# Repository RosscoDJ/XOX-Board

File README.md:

# XOX-Board
xox style board with 16 buttons and 16 less connected to two MCP23017 I/O extenders for I2C communications with micro controllers. Full Schmitt trigger hardware debouncing per button, and SMD jumper pads for addressing MCP23017 IC's on board.

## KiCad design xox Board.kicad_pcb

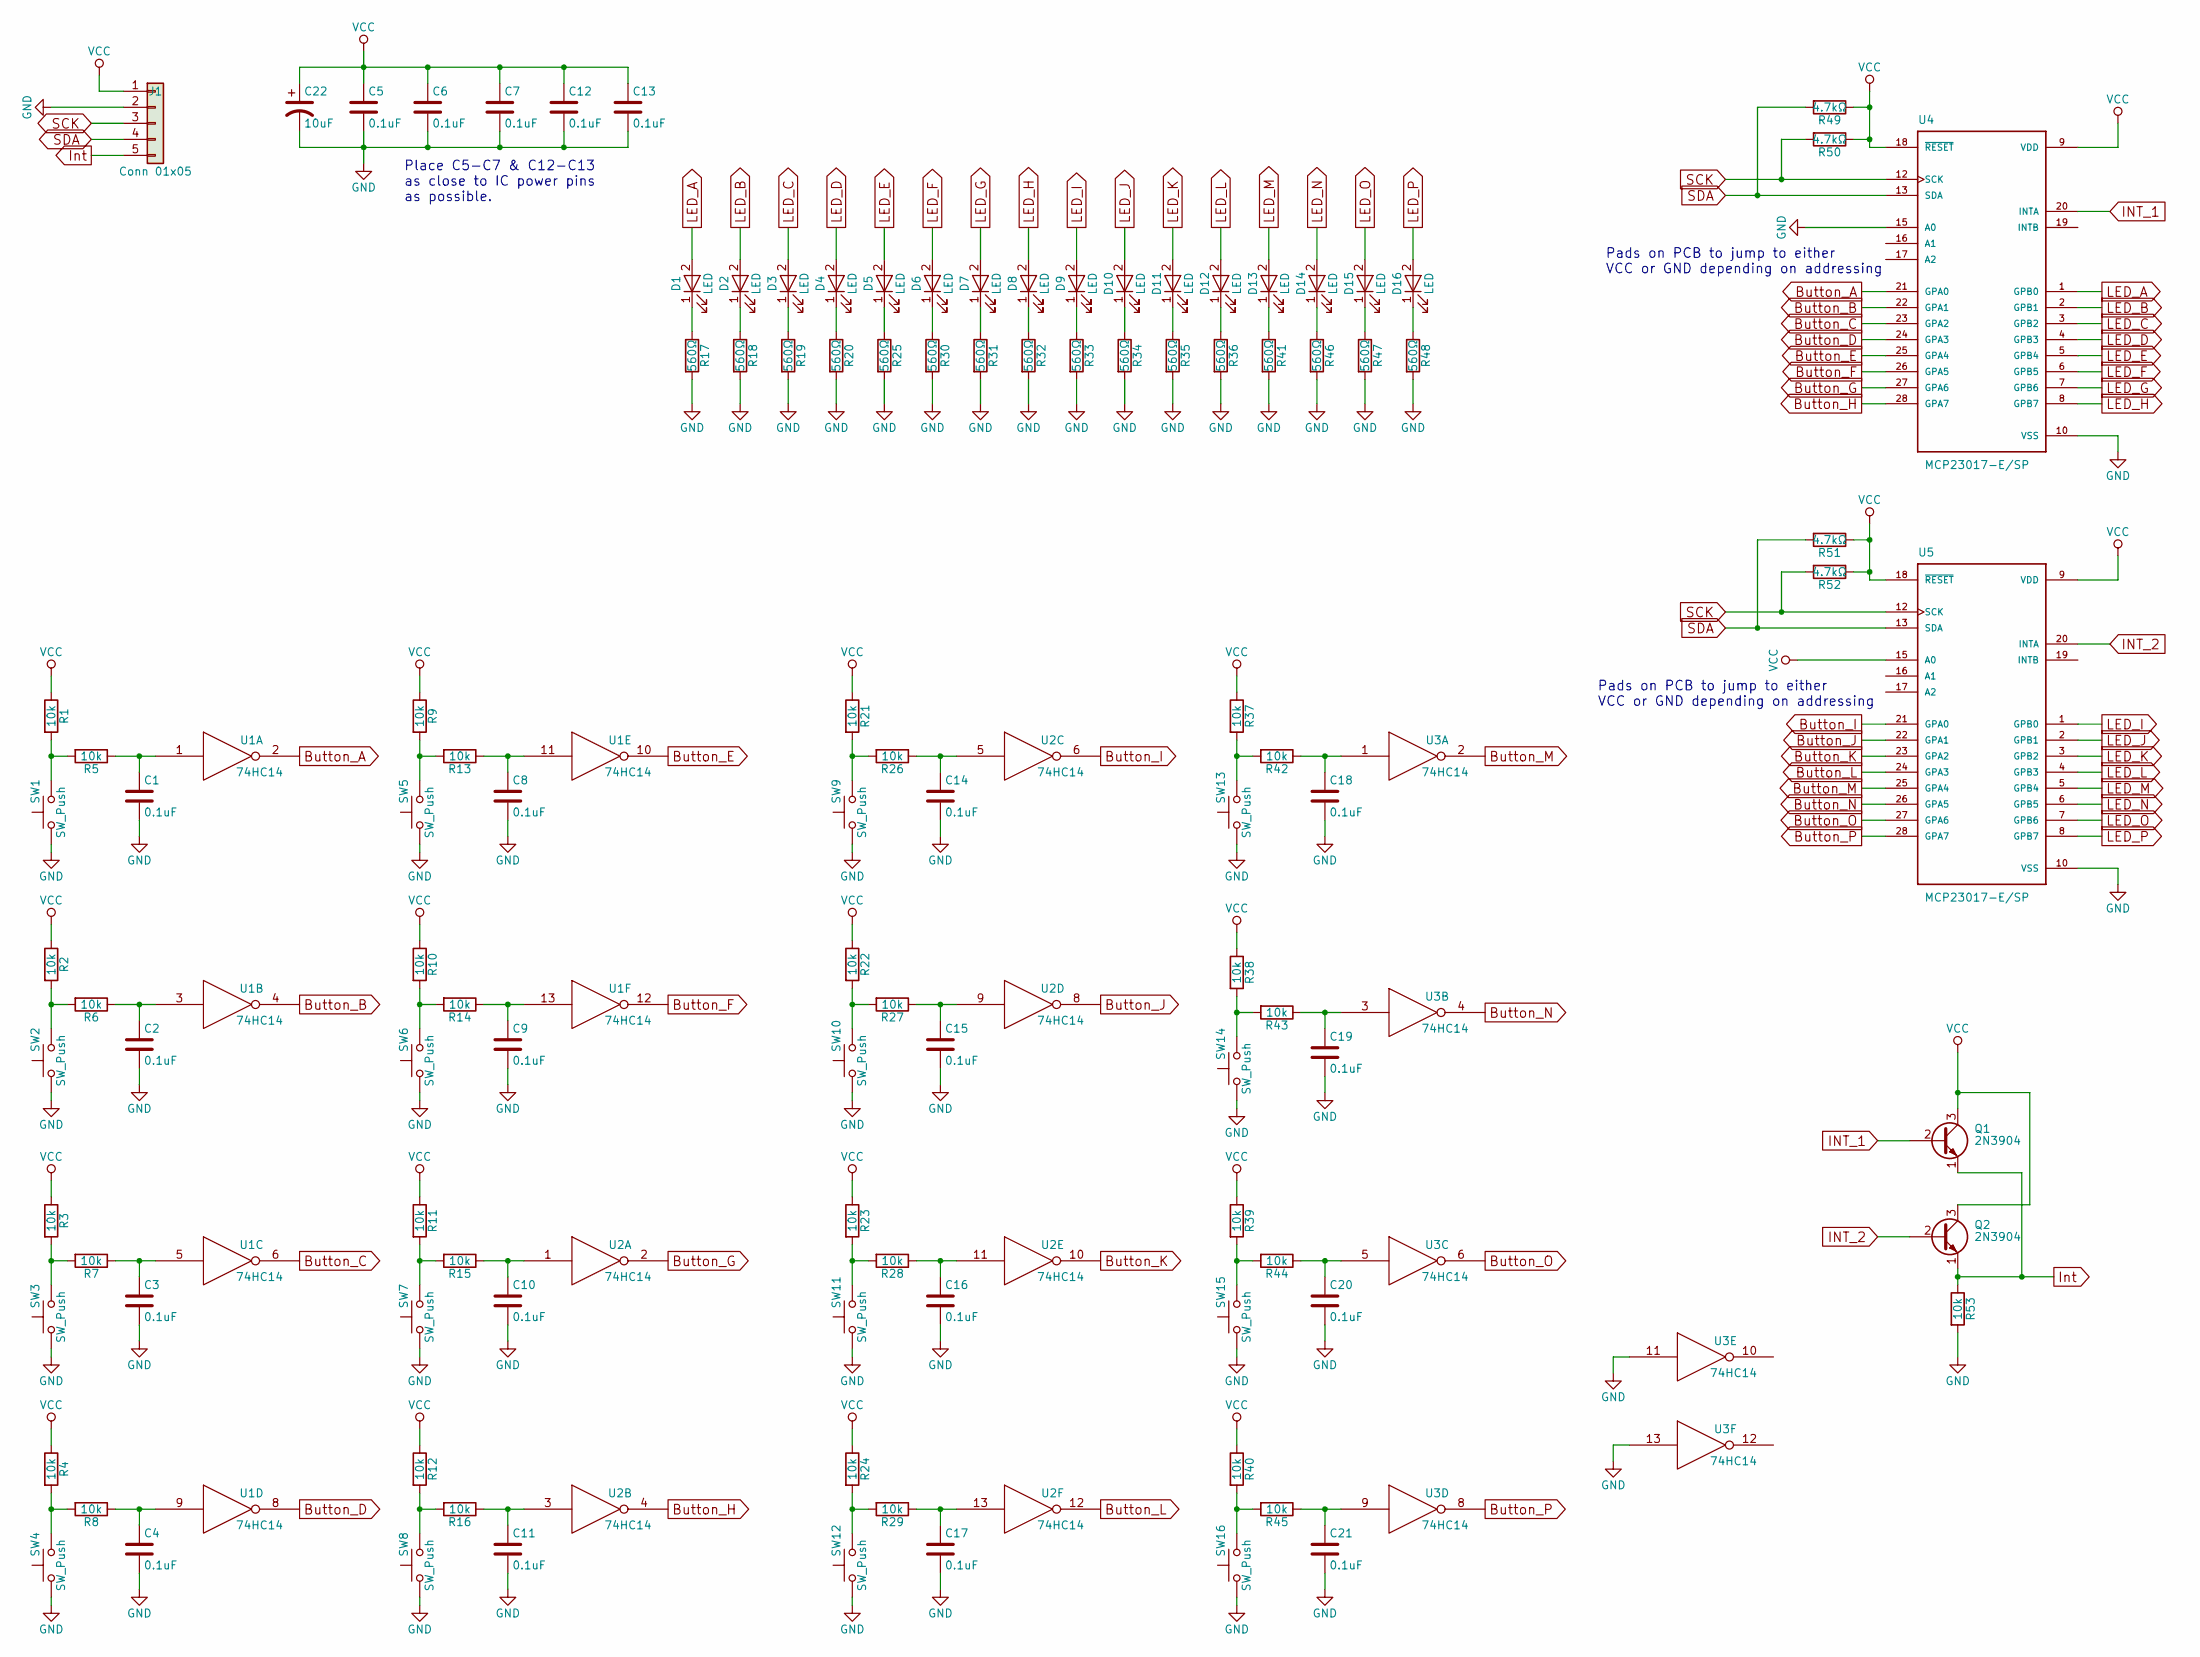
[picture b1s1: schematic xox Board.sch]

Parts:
C1, C2, C3, C4, C5, C6, C7, C8, C9, C10, C11, C12, C13, C14, C15, C16, C17, C18, C19, C20, C21: 0.1uF; C_Disc_D4.3mm_W1.9mm_P5.00mm
C22: 10uF; CP_Radial_D5.0mm_P2.00mm
D1, D2, D3, D4, D5, D6, D7, D8, D9, D10, D11, D12, D13, D14, D15, D16: LED; LED_D5.0mm
J1: Conn 01x05; Pin_Header_Straight_1x05_Pitch2.54mm
Q1, Q2: 2N3904; TO-92_Inline_Narrow_Oval
R1, R2, R3, R4, R5, R6, R7, R8, R9, R10, R11, R12, R13, R14, R15, R16, R21, R22, R23, R24, R26, R27, R28, R29, R37, R38, R39, R40, R42, R43, R44, R45, R53: 10k; R_Axial_DIN0207_L6.3mm_D2.5mm_P7.62mm_Horizontal
R17, R18, R19, R20, R25, R30, R31, R32, R33, R34, R35, R36, R41, R46, R47, R48: 560Ω; R_Axial_DIN0207_L6.3mm_D2.5mm_P7.62mm_Horizontal
R49, R50, R51, R52: 4.7kΩ; R_Axial_DIN0207_L6.3mm_D2.5mm_P7.62mm_Horizontal
SW1, SW2, SW3, SW4, SW5, SW6, SW7, SW8, SW9, SW10, SW11, SW12, SW13, SW14, SW15, SW16: SW_Push; SW_TH_Tactile_Omron_B3F-10xx
U1, U2, U3: 74HC14; DIP-14_W7.62mm_Socket
U4, U5: MCP23017-E/SP; DIP-28_W7.62mm_Socket

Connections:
Button_A: U1.2, U4.21 (GPA0)
Button_B: U1.4, U4.22 (GPA1)
Button_C: U1.6, U4.23 (GPA2)
Button_D: U1.8, U4.24 (GPA3)
Button_E: U1.10, U4.25 (GPA4)
Button_F: U1.12, U4.26 (GPA5)
Button_G: U2.2, U4.27 (GPA6)
Button_H: U2.4, U4.28 (GPA7)
Button_I: U2.6, U5.21 (GPA0)
Button_J: U2.8, U5.22 (GPA1)
Button_K: U2.10, U5.23 (GPA2)
Button_L: U2.12, U5.24 (GPA3)
Button_M: U3.2, U5.25 (GPA4)
Button_N: U3.4, U5.26 (GPA5)
Button_O: U3.6, U5.27 (GPA6)
Button_P: U3.8, U5.28 (GPA7)
GND: C1.2, C2.2, C3.2, C4.2, C5.2, C6.2, C7.2, C8.2, C9.2, C10.2, C11.2, C12.2, C13.2, C14.2, C15.2, C16.2, C17.2, C18.2, C19.2, C20.2, C21.2, C22.2, J1.2, R17.2, R18.2, R19.2, R20.2, R25.2, R30.2, R31.2, R32.2, R33.2, R34.2, R35.2, R36.2, R41.2, R46.2, R47.2, R48.2, R53.2, SW1.1, SW2.1, SW3.1, SW4.1, SW5.1, SW6.1, SW7.1, SW8.1, SW9.1, SW10.1, SW11.1, SW12.1, SW13.1, SW14.1, SW15.1, SW16.1, U1.7 (GND), U2.7 (GND), U3.7 (GND), U3.11, U3.13, U4.10 (VSS), U4.15 (A0), U5.10 (VSS)
INT_1: Q1.2 (B), U4.20 (INTA)
INT_2: Q2.2 (B), U5.20 (INTA)
Int: J1.5, Q1.1 (E), Q2.1 (E), R53.1
LED_A: D1.2 (A), U4.1 (GPB0)
LED_B: D2.2 (A), U4.2 (GPB1)
LED_C: D3.2 (A), U4.3 (GPB2)
LED_D: D4.2 (A), U4.4 (GPB3)
LED_E: D5.2 (A), U4.5 (GPB4)
LED_F: D6.2 (A), U4.6 (GPB5)
LED_G: D7.2 (A), U4.7 (GPB6)
LED_H: D8.2 (A), U4.8 (GPB7)
LED_I: D9.2 (A), U5.1 (GPB0)
LED_J: D10.2 (A), U5.2 (GPB1)
LED_K: D11.2 (A), U5.3 (GPB2)
LED_L: D12.2 (A), U5.4 (GPB3)
LED_M: D13.2 (A), U5.5 (GPB4)
LED_N: D14.2 (A), U5.6 (GPB5)
LED_O: D15.2 (A), U5.7 (GPB6)
LED_P: D16.2 (A), U5.8 (GPB7)
unnamed: C1.1, R5.1, U1.1
unnamed: C2.1, R6.1, U1.3
unnamed: C3.1, R7.1, U1.5
unnamed: C4.1, R8.1, U1.9
unnamed: C8.1, R13.1, U1.11
unnamed: C9.1, R14.1, U1.13
unnamed: C10.1, R15.1, U2.1
unnamed: C11.1, R16.1, U2.3
unnamed: C14.1, R26.1, U2.5
unnamed: C15.1, R27.1, U2.9
unnamed: C16.1, R28.1, U2.11
unnamed: C17.1, R29.1, U2.13
unnamed: C18.1, R42.1, U3.1
unnamed: C19.1, R43.1, U3.3
unnamed: C20.1, R44.1, U3.5
unnamed: C21.1, R45.1, U3.9
unnamed: D1.1 (K), R17.1
unnamed: D2.1 (K), R18.1
unnamed: D3.1 (K), R19.1
unnamed: D4.1 (K), R20.1
unnamed: D5.1 (K), R25.1
unnamed: D6.1 (K), R30.1
unnamed: D7.1 (K), R31.1
unnamed: D8.1 (K), R32.1
unnamed: D9.1 (K), R33.1
unnamed: D10.1 (K), R34.1
unnamed: D11.1 (K), R35.1
unnamed: D12.1 (K), R36.1
unnamed: D13.1 (K), R41.1
unnamed: D14.1 (K), R46.1
unnamed: D15.1 (K), R47.1
unnamed: D16.1 (K), R48.1
unnamed: R1.2, R5.2, SW1.2
unnamed: R2.2, R6.2, SW2.2
unnamed: R3.2, R7.2, SW3.2
unnamed: R4.2, R8.2, SW4.2
unnamed: R10.2, R14.2, SW6.2
unnamed: R11.2, R15.2, SW7.2
unnamed: R12.2, R16.2, SW8.2
unnamed: R9.2, R13.2, SW5.2
unnamed: R21.2, R26.2, SW9.2
unnamed: R22.2, R27.2, SW10.2
unnamed: R23.2, R28.2, SW11.2
unnamed: R24.2, R29.2, SW12.2
unnamed: R37.2, R42.2, SW13.2
unnamed: R38.2, R43.2, SW14.2
unnamed: R39.2, R44.2, SW15.2
unnamed: R40.2, R45.2, SW16.2
SCK: J1.3, R50.2, R52.2, U4.12 (SCK), U5.12 (SCK)
SDA: J1.4, R49.2, R51.2, U4.13 (SDA), U5.13 (SDA)
VCC: C5.1, C6.1, C7.1, C12.1, C13.1, C22.1, J1.1, Q1.3 (C), Q2.3 (C), R1.1, R2.1, R3.1, R4.1, R9.1, R10.1, R11.1, R12.1, R21.1, R22.1, R23.1, R24.1, R37.1, R38.1, R39.1, R40.1, R49.1, R50.1, R51.1, R52.1, U1.14 (VCC), U2.14 (VCC), U3.14 (VCC), U4.9 (VDD), U4.18 (~RESET~), U5.9 (VDD), U5.15 (A0), U5.18 (~RESET~)

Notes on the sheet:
Place C5-C7 & C12-C13 as close to IC power pins as possible.
Pads on PCB to jump to either VCC or GND depending on addressing

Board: 2 copper layers, 115 parts (0 on the bottom side), 87 nets, no tracks yet.

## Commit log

2018-05-09 Add files via upload
    Add kicad files for project.
